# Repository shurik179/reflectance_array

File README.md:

# Reflectance array
This repository contains code, hardware design files and more  for a 6-sensor reflectance line array with i2c interface. 
It is work in progress.

Structure of the repository:
- docs: source files for readthedocs documentation 
- hardware: board design files (KiCad8)
- firmware: board firmware (Arduino sketch,using [megatinycore Arduino core](https://github.com/SpenceKonde/megaTinyCore))
- python_lib: library for using the sensor (Micropython/CircuitPython)
- 3d printed: various 3d printed mounts (including a mount for XRP robot)

## Features:
- 6 long-range reflectance sensors 
- built-in MCU (attiny1616) takes care of reading the sensors and computing the calibrated reading 
- i2c interface; supports normal (100k) and fast (400k) speeds
- can be connected using [qwiic/stemma qt](https://www.sparkfun.com/qwiic) connector or standard 0.1" headers (need to be soldered)
- can be calibrated, setting black and white values for each sensor individually. Calibration values are preserved even when the sensor is powered off 
- built-in computation of line position for line following applications; supports white on black and black on white lines 
- built-in I2C pullups (3.3k) on SDA, SCL lines. Can be disabled by cutting open the solder bridge labeled "I2C pullups"
- configurable I2C address
- provided library for use with micropython/circuitpython (Arduino library coming soon)

All of the above is distributed under open source license (MIT). See LICENSE file in this repository for details. 

Detailed description and user guide can be found at https://reflectance-array.readthedocs.io/

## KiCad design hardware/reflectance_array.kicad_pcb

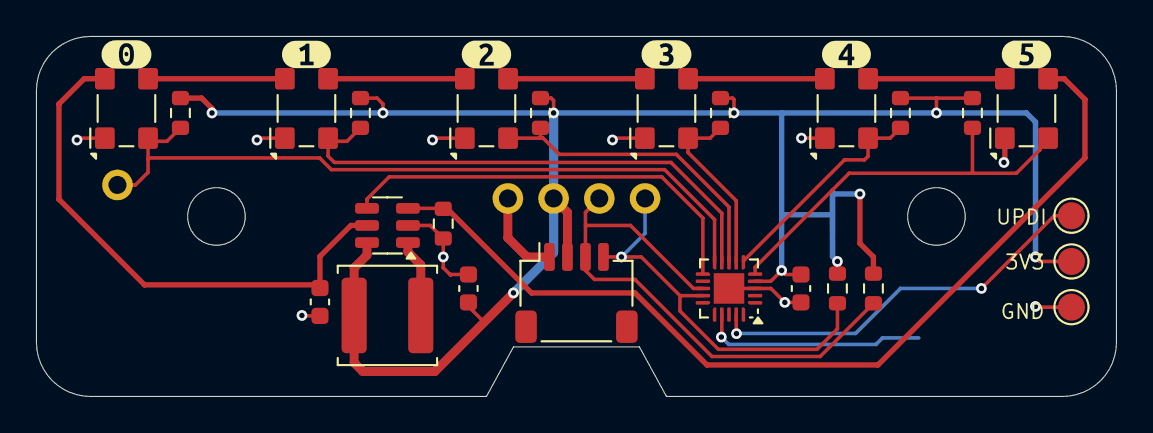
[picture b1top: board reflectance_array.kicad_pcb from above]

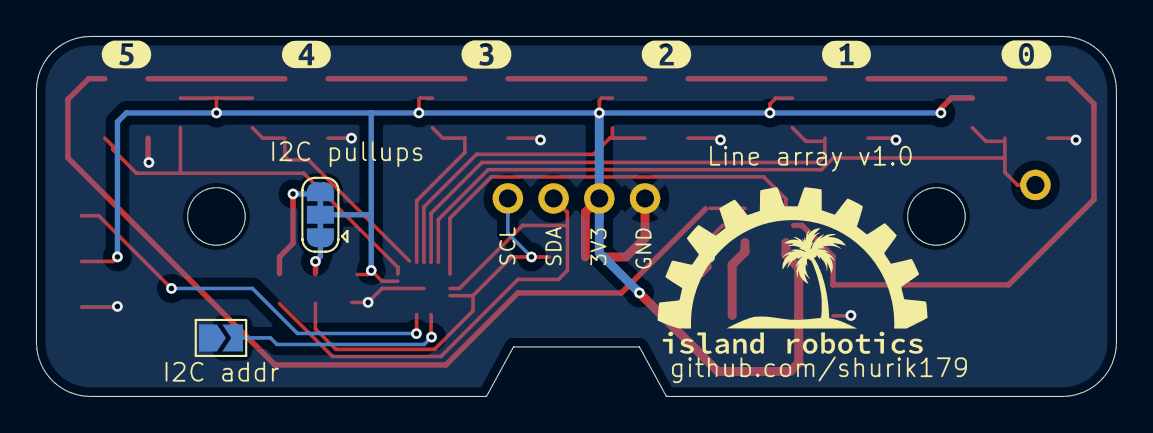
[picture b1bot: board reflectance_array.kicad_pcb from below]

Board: 2 copper layers, 60.0 x 20.0 mm, 41 parts (9 on the bottom side), 21 nets.

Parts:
C1, C2: 1uF; C_0603_1608Metric
C3: 100nF; C_0603_1608Metric
J1: Conn_01x01_Pin; connector-1p-generic-nosilk
J2: Conn_01x04_Pin; JST_SH_SM04B-SRSS-TB_1x04-1MP_P1.00mm_Horizontal
J3: Conn_01x04_Pin; connector-4p-generic-nosilk
JP1: SolderJumper_2_Open; SolderJumper-2_P1.3mm_Open_TrianglePad1.0x1.5mm
JP2: SolderJumper_3_Bridged123; SolderJumper-3_P1.3mm_Bridged123_RoundedPad1.0x1.5mm
L1: 22uH; L_Sunlord_SWPA5020S
R1: 12; R_0603_1608Metric
R2, R3, R4, R5, R6, R8: 10K; R_0603_1608Metric
R7, R9: 3.3K; R_0603_1608Metric
TP1, TP2, TP3: TestPoint; TestPoint_Pad_D1.5mm
U1: AP3019A; TSOT-23-6
U2, U3, U5, U6, U7, U8: ITR1502SR40A; Everlight_ITR1502SR40A
U4: ATtiny1616-M; VQFN-20-1EP_3x3mm_P0.4mm_EP1.7x1.7mm
kibuzzard-67E182C9: G***; kibuzzard-67E182C9
kibuzzard-67E182D6: G***; kibuzzard-67E182D6
kibuzzard-67E182E1: G***; kibuzzard-67E182E1
kibuzzard-67E182EE: G***; kibuzzard-67E182EE
kibuzzard-67E182F6: G***; kibuzzard-67E182F6
kibuzzard-67E1830C: G***; kibuzzard-67E1830C
kibuzzard-67E1831D: G***; kibuzzard-67E1831D
kibuzzard-67E1832E: G***; kibuzzard-67E1832E
kibuzzard-67E18323: G***; kibuzzard-67E18323
kibuzzard-67E18328: G***; kibuzzard-67E18328
kibuzzard-67E18337: G***; kibuzzard-67E18337
kibuzzard-67E18343: G***; kibuzzard-67E18343

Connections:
+3V3: C1.1, C3.1, J2.2, J3.2, JP2.1 (A), JP2.2 (C), JP2.3 (B), L1.1, R2.1, R3.1, R4.1, R5.1, R6.1, R7.1, R8.1, R9.1, TP2.1, U1.6 (VIN), U4.4 (VCC)
/FB: R1.1, U1.3 (FB), U8.3 (K)
/I2C_ADDR: JP1.2 (B), U4.17 (PC2)
/LED_ENABLE: U1.4 (CTRL), U4.11 (PB3)
/S0: J1.1, R2.2, U2.2, U4.10 (PB4)
/S1: R3.2, U3.2, U4.9 (PB5)
/S2: R4.2, U4.8 (PA7), U5.2
/S3: R5.2, U4.7 (PA6), U6.2
/S4: R6.2, U4.6 (PA5), U7.2
/S5: R8.2, U4.5 (PA4), U8.2
/SCL: J2.4, J3.4, R7.2, U4.14 (PB0)
/SDA: J2.3, J3.3, R9.2, U4.13 (PB1)
/UPDI: TP1.1, U4.19 (~RESET/PA0)
/VCC_LED: C2.1, U1.5 (VOUT), U2.4 (A)
GNDREF: C1.2, C2.2, C3.2, J2.1, J3.1, JP1.1 (A), R1.2, TP3.1, U1.2 (GND), U2.1, U3.1, U4.3 (GND), U4.21 (GND), U5.1, U6.1, U7.1, U8.1
unnamed: L1.2, U1.1 (SW)
unnamed: U2.3 (K), U3.4 (A)
unnamed: U3.3 (K), U5.4 (A)
unnamed: U5.3 (K), U6.4 (A)
unnamed: U6.3 (K), U7.4 (A)
unnamed: U7.3 (K), U8.4 (A)

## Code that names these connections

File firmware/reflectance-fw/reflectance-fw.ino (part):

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//firmware version 
#define FW_MINOR 0
#define FW_MAJOR 1
#define PIN_ENABLE PIN_PB3
#define PIN_ADDR PIN_PC2 //for changing I2C address

#define NUM_SENSORS 6
#define NUM_REGISTERS 60 //size of register bank, in bytes
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#define REG_CALIBRATIONS 32 //start of calibration data, 4 bytes per sensor: black low byte, black high, white low, white high


uint8_t SensorPins[NUM_SENSORS] = { PIN_PB4, PIN_PB5, PIN_PA7, PIN_PA6, PIN_PA5, PIN_PA4 };
uint16_t BlackCalibration[NUM_SENSORS] = {120,120,120,120,120,120};
uint16_t WhiteCalibration[NUM_SENSORS] = {980,980,980, 980, 980,980};

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
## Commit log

2025-03-24 first draft version
2025-03-24 version 0.1
2025-04-05 version 1.0
2025-04-14 added firmware README
2025-04-23 adding micropython library
2025-04-23 adding docs
2025-04-23 docs update
2025-04-24 backup cleanup
2025-04-24 docs - photos added
2025-04-25 bumoing fw version to 1.0
2025-04-25 fixing stupid bug in digital reading part of firmware

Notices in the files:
firmware/reflectance-fw/reflectance-fw.ino:
SPDX-FileCopyrightText: Copyright 2025 Alexander Kirillov <shurik179@gmail.com>
SPDX-License-Identifier: MIT
